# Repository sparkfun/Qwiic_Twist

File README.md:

SparkFun Qwiic Twist 
===========================================================

[*SparkFun Qwiic Twist (DEV-15083)*](https://www.sparkfun.com/products/15083)

Sometimes you just need a volume knob. The Qwiic Twist is a digital RGB encoder. What does that mean? The Twist takes care of all the various interrupts, switches, PWM'ing of LEDs and presents all those features over an easy-to-use I<sup>2</sup>C interface. The Qwiic Twist was designed to get rid of the large mass of wires that are needed to implement an RGB encoder in a breadboard. Stop messing around with interrupt debugging and get back to your project!

One rotation in the clockwise direction increases the overall count by 24 and -24 in the counter clockwise direction. The number of 'ticks' or steps the user has turned the knob are transmitted over I2C. Additionally, the red, green, and blue LEDs are all set via software commands and can be digitally mixed to achieve over 16 million colors. 

We designed Qwiic Twist with an indent encoder which gives the user a great 'clicky' feel. Additionally, the encoder has a built in button so the user can select an GUI menu or element by pressing on the encoder.

The I2C address of Qwiic Twist is software configurable which means you can hookup over 100 on a single I2C bus!

Repository Contents
-------------------

* **/Documents** - Datasheet for the Qwiic Twist 
* **/Firmware/Qwiic_Twist** - Firmware for the Qwiic Twist
* **Hardware** - .brd and .sch for Qwiic Twist 

Documentation
--------------
* **[Qwiic Twist Hookup Guide](https://learn.sparkfun.com/tutorials/qwiic-twist-hookup-guide)** - Hookup guide for the Qwiic Twist
* **[Qwiic Twist Arduino Library](https://github.com/sparkfun/SparkFun_Qwiic_Twist_Arduino_Library)** - Arduino Library for the Qwiic Twist
* **[Installing an Arduino Library Guide](https://learn.sparkfun.com/tutorials/installing-an-arduino-library)** - Basic information on how to install an Arduino library.
* **[Product Repository](https://github.com/sparkfun/Qwiic_Twist)** - Main repository (including hardware files)

License Information
-------------------

This product is _**open source**_! 

Please review the LICENSE.md file for license information. 

If you have any questions or concerns on licensing, please visit the [SparkFun Forum](https://forum.sparkfun.com/index.php) and post a topic. For more general questions related to our qwiic system, please visit this section of the forum: [SparkFun Forums: QWIIC SYSTEMS](https://forum.sparkfun.com/viewforum.php?f=105)

Please use, reuse, and modify these files as you see fit. Please maintain attribution to SparkFun Electronics and release any derivative under the same license.

Distributed as-is; no warranty is given.
- Your friends at SparkFun.

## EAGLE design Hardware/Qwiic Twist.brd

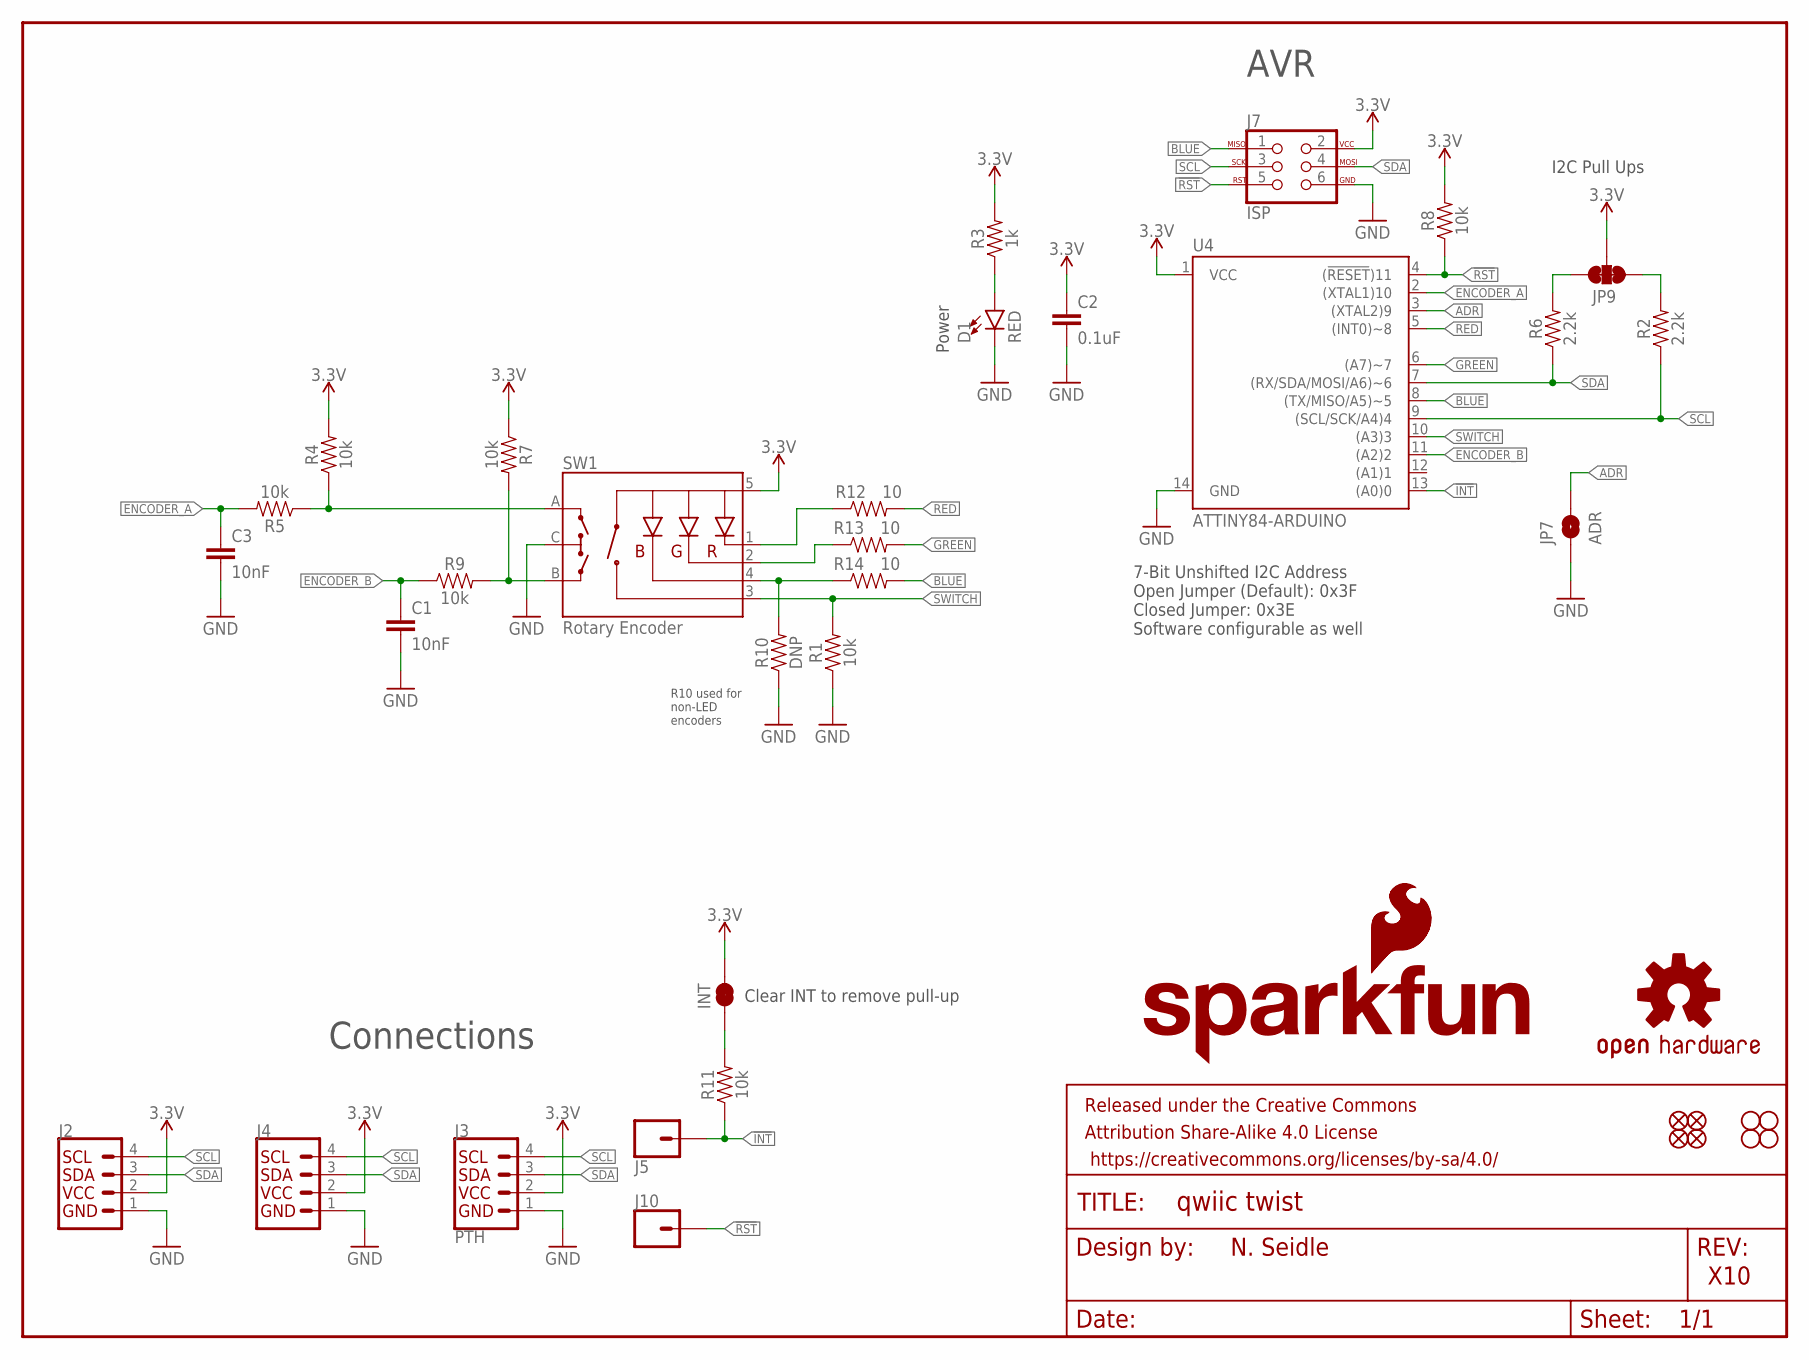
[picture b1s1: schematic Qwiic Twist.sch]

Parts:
C1, C3: 10nF; 0603
C2: 0.1uF; 0603
D1: RED; LED-0603
FRAME1: FRAME-LETTER; CREATIVE_COMMONS
INT: JUMPER-SMT_2_NC_TRACE_SILK; SMT-JUMPER_2_NC_TRACE_SILK
J2, J4: QWIIC_CONNECTORJS-1MM; 1X04_1MM_RA
J3: PTH; 1X04_NO_SILK
J5, J10: CONN_01PTH_NO_SILK_YES_STOP; 1X01_NO_SILK
J7: ISP; 2X3_TEST_POINTS
JP1, JP2, JP5, JP6: FIDUCIALUFIDUCIAL; MICRO-FIDUCIAL
JP3, JP4, JP11, JP13: STAND-OFF
JP7: ADR; SMT-JUMPER_2_NO_SILK
JP9: JUMPER-SMT_3_2-NC_TRACE_SILK; SMT-JUMPER_3_2-NC_TRACE_SILK
LOGO1: OSHW-LOGOMINI; OSHW-LOGO-MINI
LOGO2: SFE_LOGO_NAME_FLAME.1_INCH; SFE_LOGO_NAME_FLAME_.1
LOGO3: SFE_LOGO_FLAME.1EXP; SFE_LOGO_FLAME_COPPER_EXPOSED_.1
R1, R4, R5, R7, R8, R9, R11: 10k; 0603
R2, R6: 2.2k; 0603
R3: 1k; 0603
R10: DNP; 0603
R12, R13, R14: 10; 0603
SW1: Rotary Encoder; ENCODER_LED_3_KIT
U4: ATTINY84-ARDUINO; SO14

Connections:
3.3V: C2.1, INT.2, J2.2, J3.2 (VCC), J4.2, J7.2, JP9.2, R3.2, R4.2, R7.1, R8.2, SW1.5 (+), U4.1 (VCC)
!INT: J5.1, R11.1, U4.13 ((A0)0)
!RST: J7.5, J10.1, R8.1, U4.4 ((!RESET!)11)
A: R4.1, R5.1, SW1.A
ADR: JP7.2, U4.3 ((XTAL2)9)
B: R7.2, R9.2, SW1.B
BLUE: J7.1, R14.2, U4.8 ((TX/MISO/A5)~5)
BLUE_RAW: R10.2, R14.1, SW1.4 (-B)
ENCODER_A: C3.1, R5.2, U4.2 ((XTAL1)10)
ENCODER_B: C1.1, R9.1, U4.11 ((A2)2)
GND: C1.2, C2.2, C3.2, D1.C, J2.1, J3.1 (GND), J4.1, J7.6, JP7.1, R1.1, R10.1, SW1.C, U4.14 (GND)
GREEN: R13.2, U4.6 ((A7)~7)
GREEN_RAW: R13.1, SW1.2 (-G)
INT_R: INT.1, R11.2
unnamed: D1.A, R3.1
RED: R12.2, U4.5 ((INT0)~8)
RED_RAW: R12.1, SW1.1 (-R)
SCL: J2.4, J3.4 (SCL), J4.4, J7.3, R2.1, U4.9 ((SCL/SCK/A4)4)
SCL_PU1: JP9.1, R2.2
SDA: J2.3, J3.3 (SDA), J4.3, J7.4, R6.1, U4.7 ((RX/SDA/MOSI/A6)~6)
SDA_PU1: JP9.3, R6.2
SWITCH: R1.2, SW1.3 (SW), U4.10 ((A3)3)

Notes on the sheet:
N. Seidle
X10
7-Bit Unshifted I2C Address Open Jumper (Default): 0x3F Closed Jumper: 0x3E Software configurable as well
I2C Pull Ups
AVR
Connections
Power
R10 used for non-LED encoders
Clear INT to remove pull-up

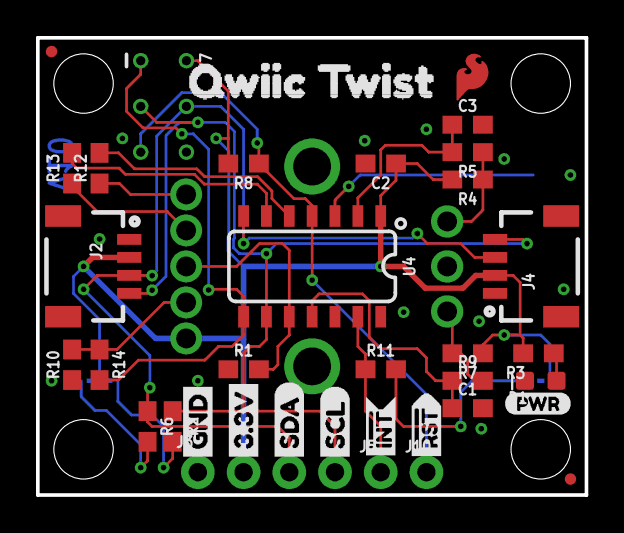
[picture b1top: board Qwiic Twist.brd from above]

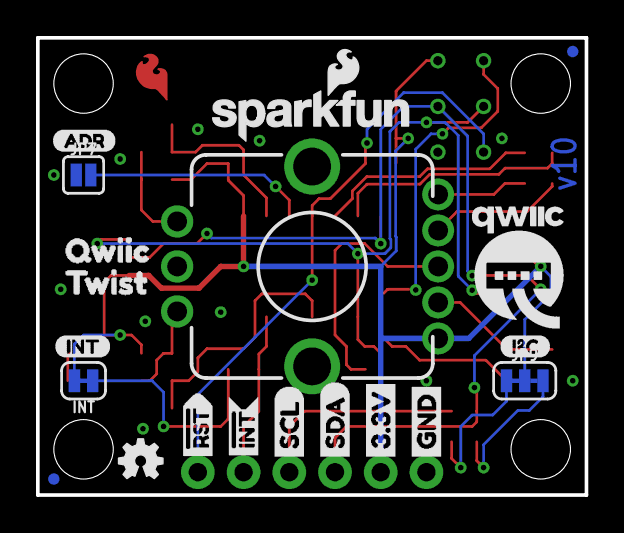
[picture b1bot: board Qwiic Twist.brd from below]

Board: 2 copper layers, 30.5 x 25.4 mm, 61 parts (20 on the bottom side), 22 nets.

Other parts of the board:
U$1: QWIIC1
U$2: INT0
U$3, U$22: GND1
U$4, U$21: 3#3V2
U$5, U$27: SDA8
U$6, U$26: SCL9
U$7, U$16: RST#-[>
U$8: I_SUPER2_C-()-03
U$9, U$11: INT#-[<
U$12: TWIST2
U$14: QWIIC_TWIST1
U$17: PWR-()-03
U$18: ADR-()-03
U$47: QWIIC-LOGO-MEDIUM

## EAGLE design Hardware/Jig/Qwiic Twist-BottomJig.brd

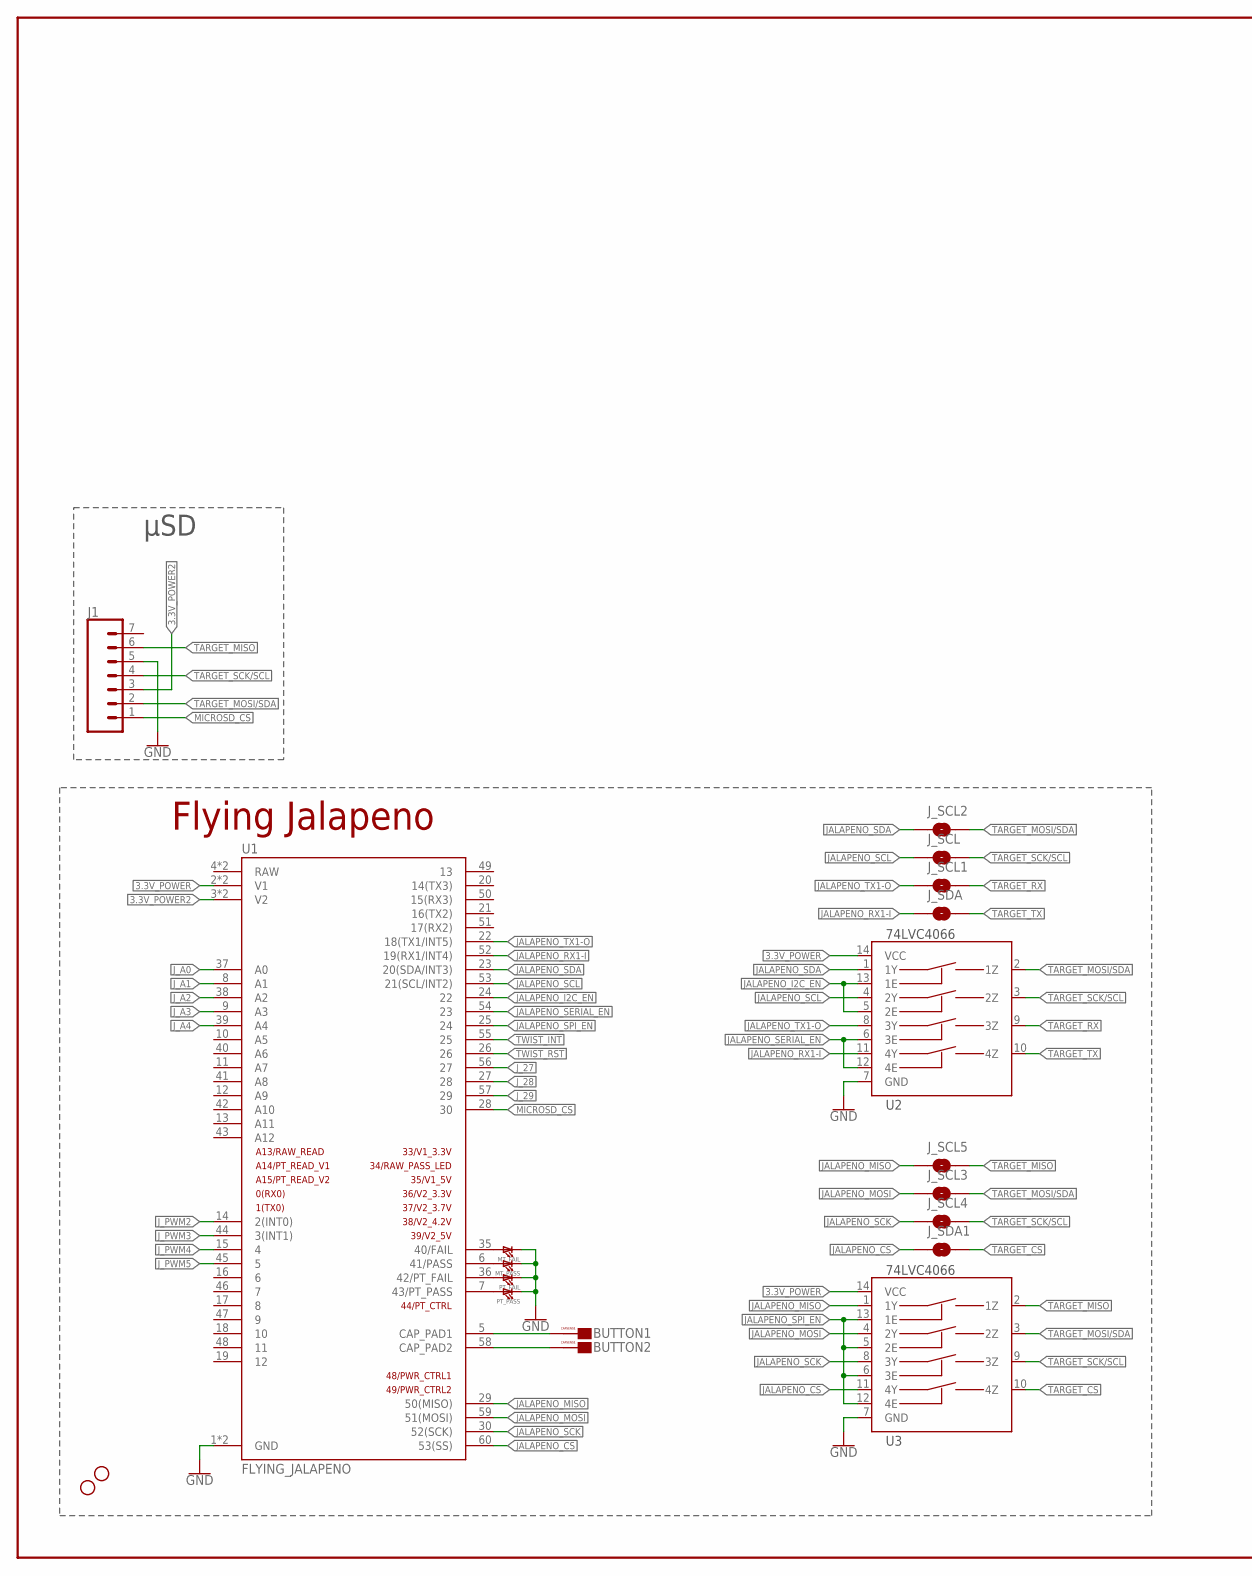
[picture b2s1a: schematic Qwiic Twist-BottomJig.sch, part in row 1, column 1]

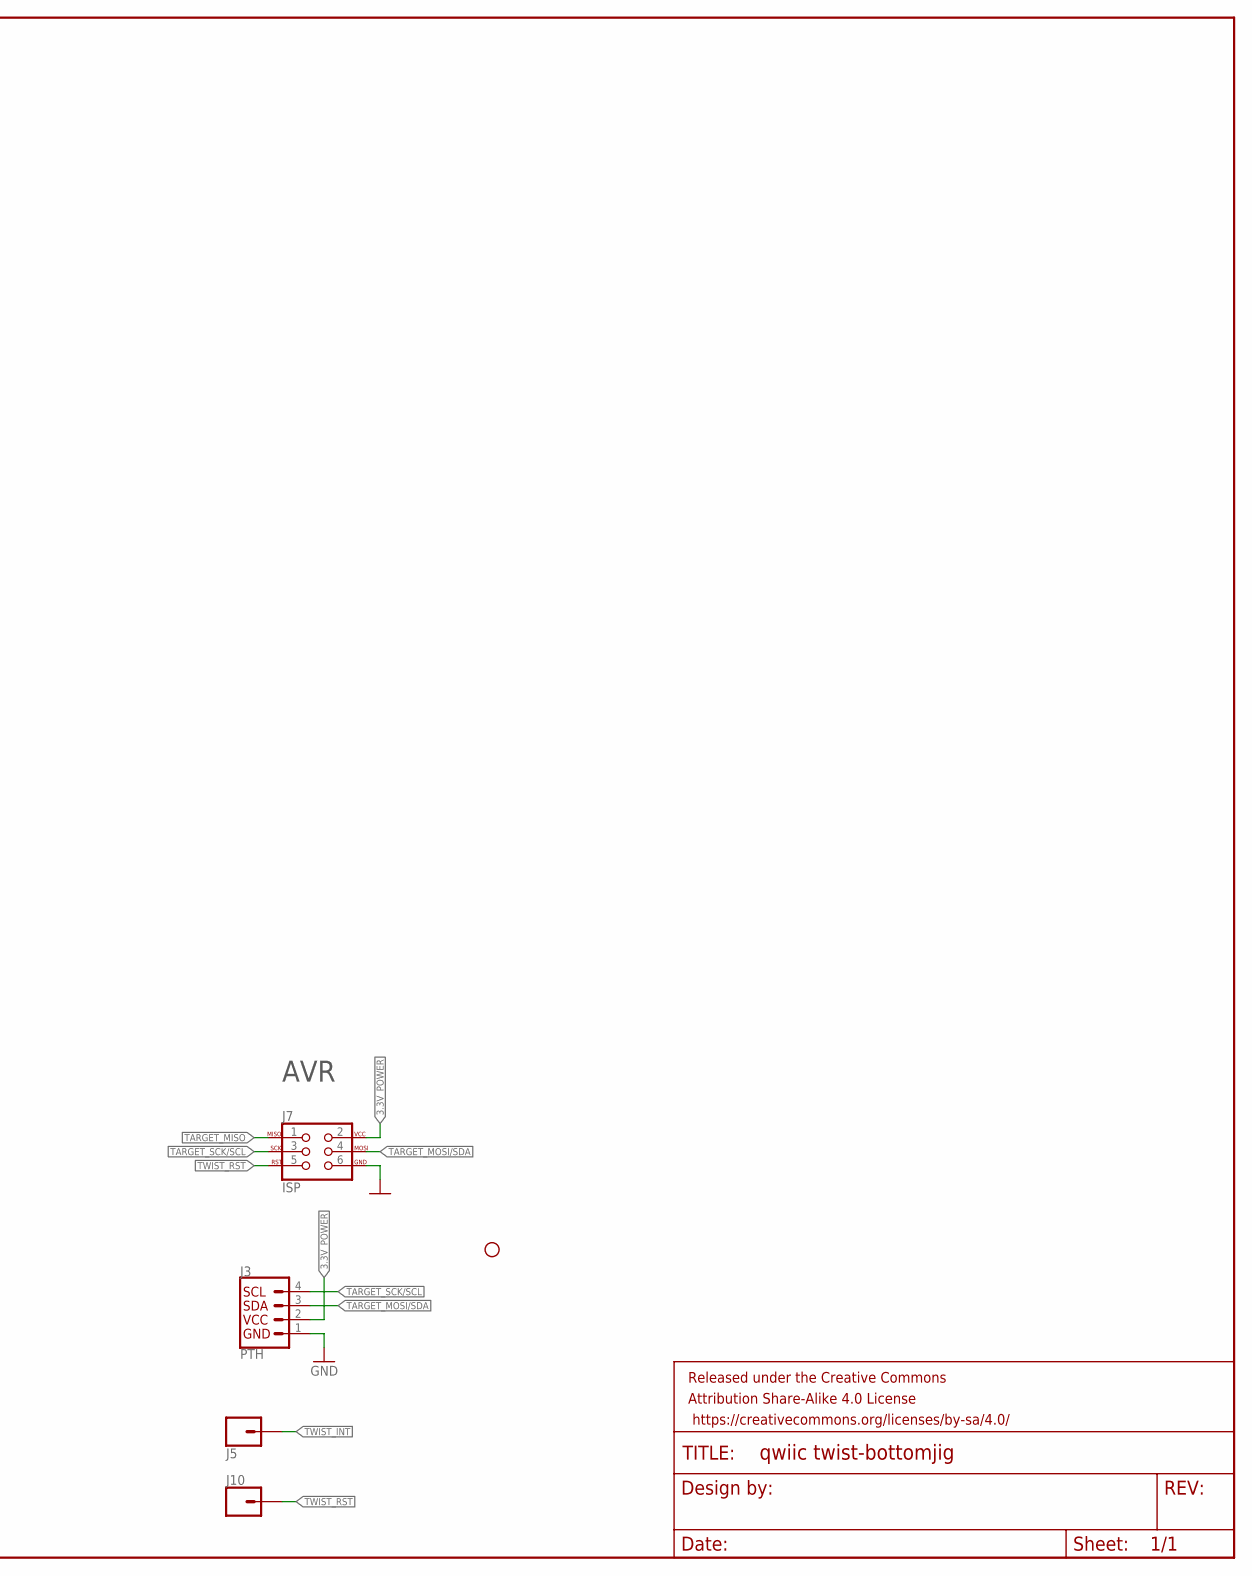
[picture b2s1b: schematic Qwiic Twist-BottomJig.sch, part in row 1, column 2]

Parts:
BUTTON1, BUTTON2: CAPSENSE_BUTTON_PAD_ONLY; CAPSENSE_BUTTON_PADS_ONLY
FRAME2: FRAME-LEDGER; CREATIVE_COMMONS
H1, H3: STAND-OFF
J1: CONN_07; 1X07
J3: PTH; 1X04_NO_SILK
J5, J10: CONN_01PTH_NO_SILK_YES_STOP; 1X01_NO_SILK
J7: ISP; 2X3-NS
JP3: STAND-OFF
J_SCL, J_SCL1, J_SCL2, J_SCL3, J_SCL4, J_SCL5: JUMPER-SMT_2_NO_NO-SILK; SMT-JUMPER_2_NO_NO-SILK
J_SDA, J_SDA1: JUMPER-SMT_2_NO_NO-SILK; SMT-JUMPER_2_NO_NO-SILK
MT_FAIL: LED1206; LED-1206
MT_PASS: LED1206; LED-1206
PT_FAIL: LED1206; LED-1206
PT_PASS: LED1206; LED-1206
U1: FLYING_JALAPENO; FLYING_JALAPENO_V3_M
U2, U3: 74LVC4066; SO14

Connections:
3.3V_POWER: J3.2 (VCC), J7.2, U1.2 (V1), U1.32 (V1), U2.14 (VCC), U3.14 (VCC)
3.3V_POWER2: J1.3, U1.3 (V2), U1.33 (V2)
BUTTON1: BUTTON1.CAPSENSE_PAD, U1.5 (CAP_PAD1)
BUTTON2: BUTTON2.CAPSENSE_PAD, U1.58 (CAP_PAD2)
GND: J1.5, J3.1 (GND), J7.6, MT_FAIL.C, MT_PASS.C, PT_FAIL.C, PT_PASS.C, U1.1 (GND), U1.31 (GND), U2.7 (GND), U3.7 (GND)
JALAPENO_CS: J_SDA1.1, U1.60 (53(SS)), U3.11 (4Y)
JALAPENO_I2C_EN: U1.24 (22), U2.5 (2E), U2.13 (1E)
JALAPENO_MISO: J_SCL5.1, U1.29 (50(MISO)), U3.1 (1Y)
JALAPENO_MOSI: J_SCL3.1, U1.59 (51(MOSI)), U3.4 (2Y)
JALAPENO_RX1-I: J_SDA.1, U1.52 (19(RX1/INT4)), U2.11 (4Y)
JALAPENO_SCK: J_SCL4.1, U1.30 (52(SCK)), U3.8 (3Y)
JALAPENO_SCL: J_SCL.1, U1.53 (21(SCL/INT2)), U2.4 (2Y)
JALAPENO_SDA: J_SCL2.1, U1.23 (20(SDA/INT3)), U2.1 (1Y)
JALAPENO_SERIAL_EN: U1.54 (23), U2.6 (3E), U2.12 (4E)
JALAPENO_SPI_EN: U1.25 (24), U3.5 (2E), U3.6 (3E), U3.12 (4E), U3.13 (1E)
JALAPENO_TX1-O: J_SCL1.1, U1.22 (18(TX1/INT5)), U2.8 (3Y)
J_27: U1.56 (27)
J_28: U1.27 (28)
J_29: U1.57 (29)
J_A0: U1.37 (A0)
J_A1: U1.8 (A1)
J_A2: U1.38 (A2)
J_A3: U1.9 (A3)
J_A4: U1.39 (A4)
J_PWM2: U1.14 (2(INT0))
J_PWM3: U1.44 (3(INT1))
J_PWM4: U1.15 (4)
J_PWM5: U1.45 (5)
MICROSD_!CS!: J1.1, U1.28 (30)
unnamed: PT_PASS.A, U1.7 (43/PT_PASS)
unnamed: PT_FAIL.A, U1.36 (42/PT_FAIL)
unnamed: MT_PASS.A, U1.6 (41/PASS)
unnamed: MT_FAIL.A, U1.35 (40/FAIL)
TARGET_CS: J_SDA1.2, U3.10 (4Z)
TARGET_MISO: J1.6, J7.1, J_SCL5.2, U3.2 (1Z)
TARGET_MOSI/SDA: J1.2, J3.3 (SDA), J7.4, J_SCL2.2, J_SCL3.2, U2.2 (1Z), U3.3 (2Z)
TARGET_RX: J_SCL1.2, U2.9 (3Z)
TARGET_SCK/SCL: J1.4, J3.4 (SCL), J7.3, J_SCL.2, J_SCL4.2, U2.3 (2Z), U3.9 (3Z)
TARGET_TX: J_SDA.2, U2.10 (4Z)
TWIST_!INT!: J5.1, U1.55 (25)
TWIST_!RST!: J7.5, J10.1, U1.26

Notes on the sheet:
AVR
Flying Jalapeno
μSD

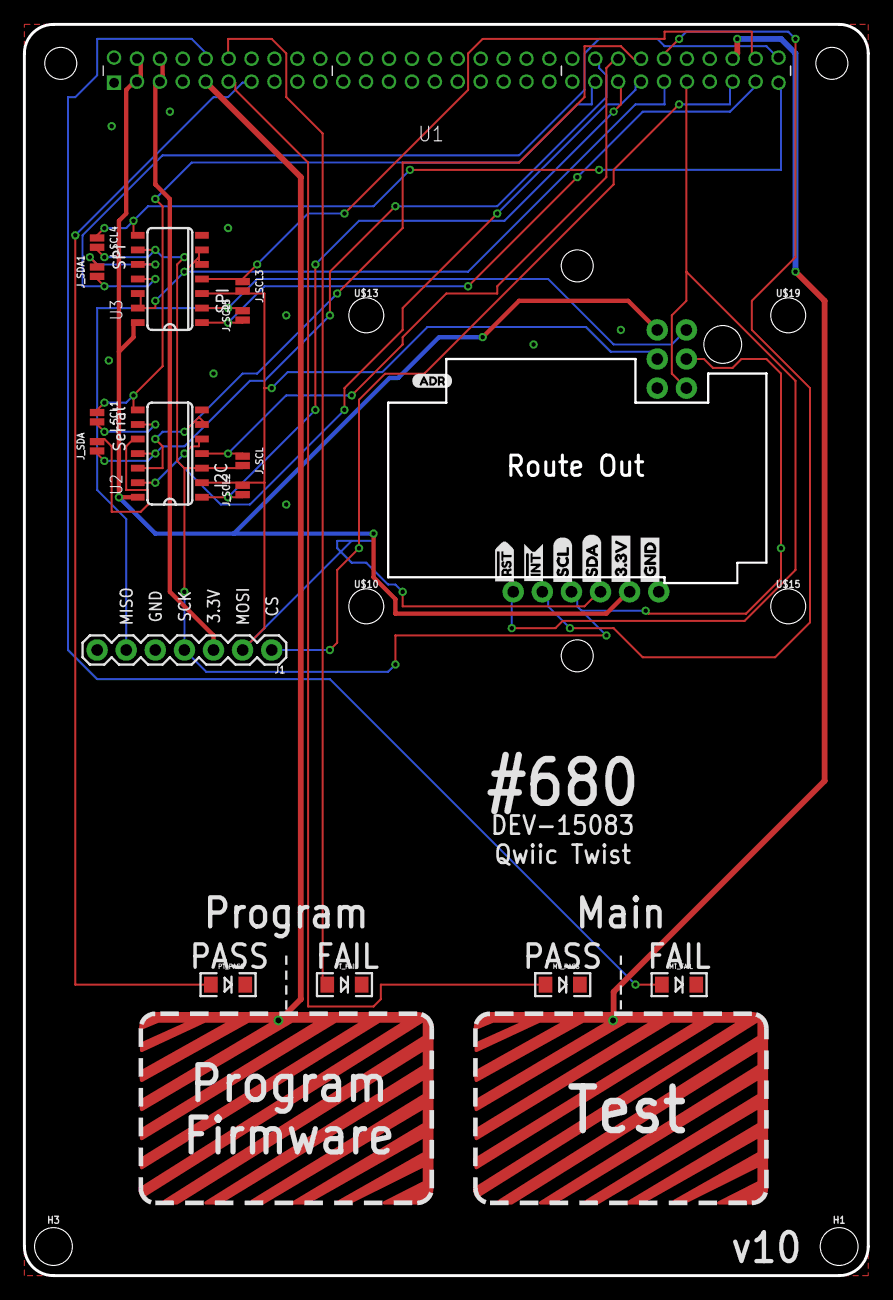
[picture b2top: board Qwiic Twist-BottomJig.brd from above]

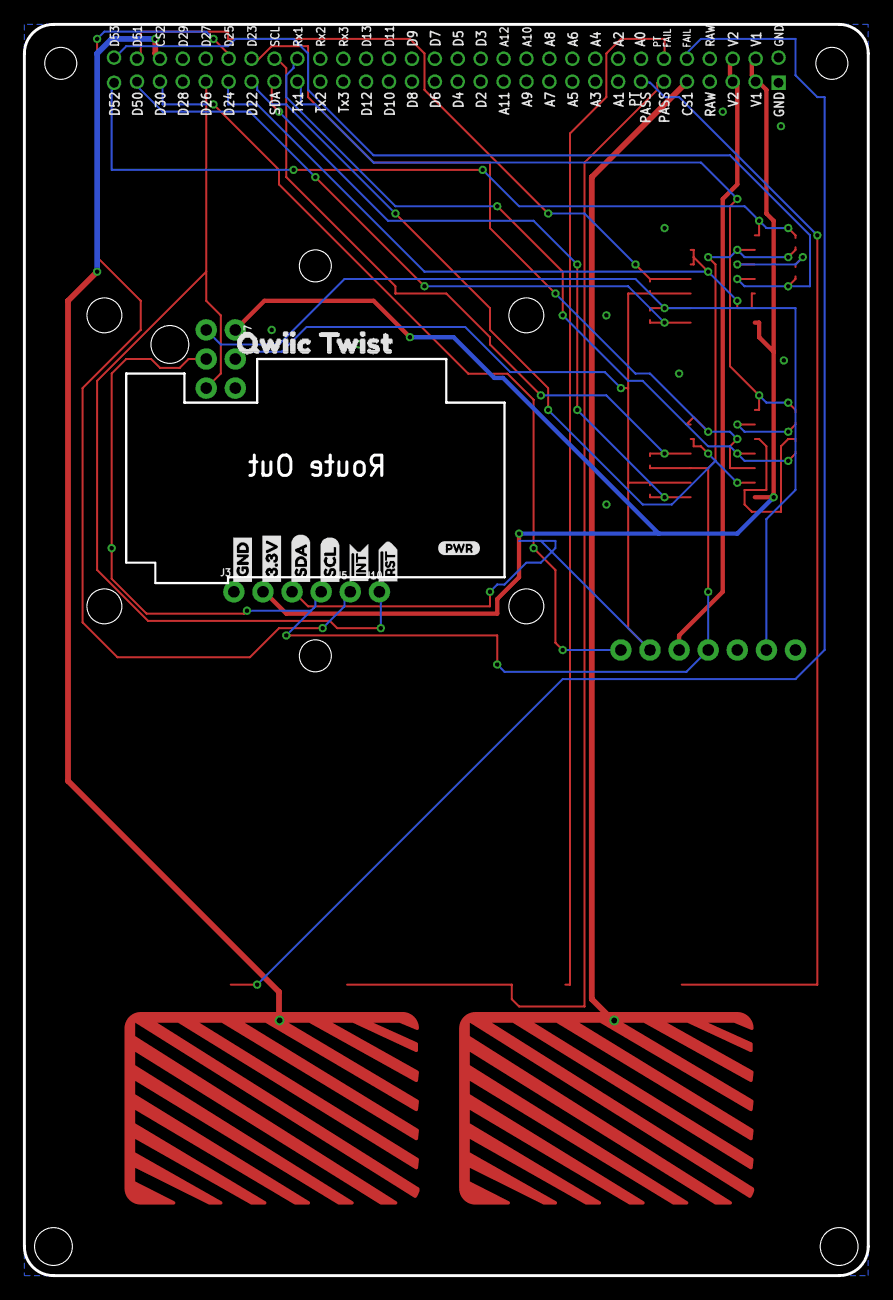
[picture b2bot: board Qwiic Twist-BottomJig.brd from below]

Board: 2 copper layers, 73.7 x 109.2 mm, 47 parts (13 on the bottom side), 29 nets.

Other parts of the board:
U$3, U$22: GND1
U$4, U$21: 3#3V2
U$5, U$27: SDA8
U$6, U$26: SCL9
U$7, U$16: RST#-[>
U$9, U$11: INT#-[<
U$10, U$13, U$15, U$19: STAND-OFF-TIGHT
U$14: QWIIC_TWIST1
U$17: PWR-()-03
U$18: ADR-()-03
U$20, U$23: NUBBIN_LOCKER

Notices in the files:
parts and their libraries:
SparkFun-Connectors: Licensing: Creative Commons ShareAlike 4.0 International - https://creativecommons.org/licenses/by-sa/4.0
SparkFun-Aesthetics: Released under the Creative Commons Attribution Share-Alike 4.0 License
SparkFun-Aesthetics: https://creativecommons.org/licenses/by-sa/4.0
